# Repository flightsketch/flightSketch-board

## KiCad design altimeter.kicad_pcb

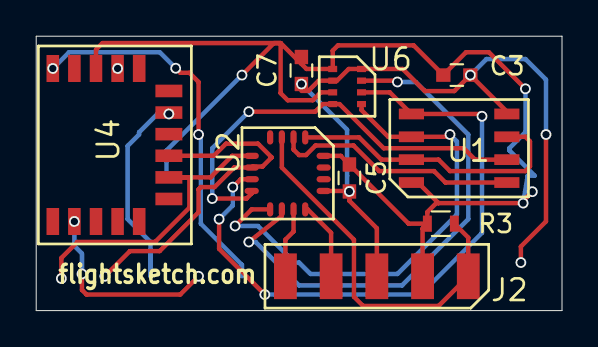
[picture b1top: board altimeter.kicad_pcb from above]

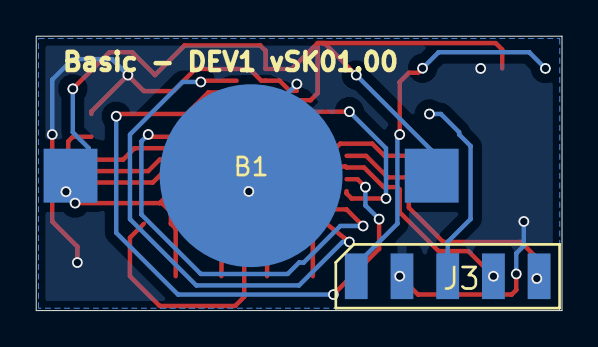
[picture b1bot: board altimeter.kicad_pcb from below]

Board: 2 copper layers, 29.2 x 15.2 mm, 11 parts (2 on the bottom side), 15 nets.

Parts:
B1: 1632-holder
C3: 10u; C_0603
C5: 0.1u; C_0603
C7: .1u; C_0603
J2, J3: Conn_01x05_Male; pin5
R3: 10k; R_0603
U1: EEPROM; SO8
U2: PIC16F15325; UQFN_16
U4: RN4871
U6: BMP280; BMP280-2

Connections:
EEPROM_CS: U1.1, U2.2
EEPROM_HOLD: U1.3, U1.7, U2.1
MCLR: J2.1, R3.1, U2.3
unnamed: J3.1, U4.16
unnamed: J3.3, U4.10
unnamed: U2.10, U6.2
PGC: J2.5, U2.11
PGD: J2.4, U2.12
SCK: U1.6, U2.9, U6.4
SDI: U1.2, U2.8, U6.5
SDO: U1.5, U2.7, U6.3
U1RX: J3.4, U2.6, U4.8
U1TX: J3.5, U2.5, U4.7
VIN: B1.2, C3.1, C5.1, C7.1, J2.2, R3.2, U1.8, U2.16, U4.14, U6.6, U6.8
VSS: B1.1, C3.2, C5.2, C7.2, J2.3, J3.2, U1.4, U2.13, U4.2, U4.13, U6.1, U6.7

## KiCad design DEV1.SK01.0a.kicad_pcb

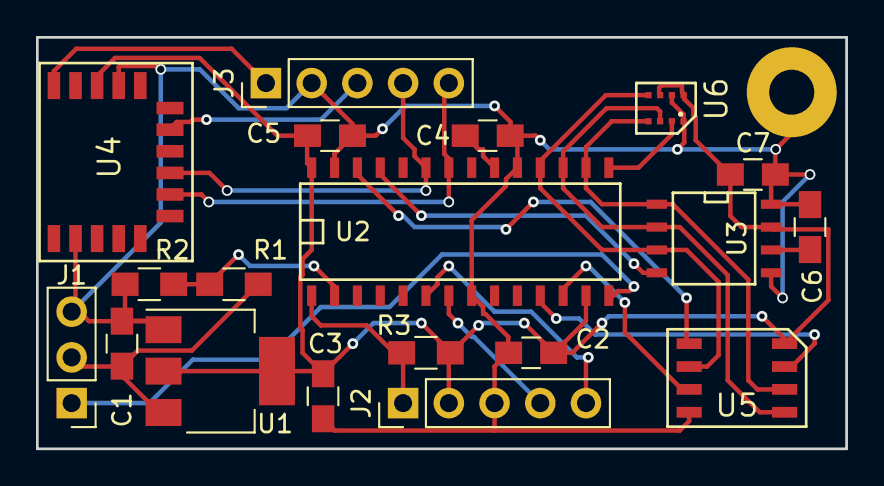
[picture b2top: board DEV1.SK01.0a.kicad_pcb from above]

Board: 2 copper layers, 45.0 x 22.9 mm, 19 parts (0 on the bottom side), 22 nets.

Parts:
C1, C3, C4: 10u; C_0805_HandSoldering
C2, C5: 0.1u; C_0805_HandSoldering
C6: 1u; C_0805_HandSoldering
C7: .1u; C_0805_HandSoldering
J1: Conn_01x03_Male; Pin_Header_Straight_1x03_Pitch2.54mm
J2, J3: Conn_01x05_Male; Pin_Header_Straight_1x05_Pitch2.54mm
R1: 200k; R_0805_HandSoldering
R2: 100k; R_0805_HandSoldering
R3: 10k; R_0805_HandSoldering
U1: LDL1117; SOT-223-3_TabPin2
U2: test; SOIC-28
U3: accel; SOIC-8-N
U4: RN4871
U5: EEPROM; SO8
U6: BMP280

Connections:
+3V3: C2.1, C3.1, C5.1, C7.1, J2.2, R3.2, U1.2, U2.13, U2.28, U3.7, U4.14, U5.8, U6.6, U6.8
DEBUG: J1.1, U2.14
MCLR: J2.1, R3.1, U2.1
unnamed: C4.1, U2.20
unnamed: C6.1, U3.6
unnamed: J3.1, U4.16
unnamed: J3.3, U4.10
unnamed: R1.1, R2.2, U2.2
unnamed: U2.11, U5.7
unnamed: U2.12, U5.3
unnamed: U2.15, U6.2
unnamed: U2.25, U3.4
unnamed: U2.26, U5.1
PGC: J2.5, U2.6
PGD: J2.4, U2.7
SCK: U2.16, U3.1, U5.6, U6.4
SDI: U2.18, U3.3, U5.2, U6.5
SDO: U2.17, U3.2, U5.5, U6.3
U1RX: J3.4, U2.23, U4.8
U1TX: J3.5, U2.22, U4.7
VIN: C1.1, J1.2, R1.2, U1.3
VSS: C1.2, C2.2, C3.2, C4.2, C5.2, C6.2, C7.2, J1.3, J2.3, J3.2, R2.1, U1.1, U2.8, U2.19, U2.27, U3.5, U3.8, U4.2, U4.13, U5.4, U6.1, U6.7

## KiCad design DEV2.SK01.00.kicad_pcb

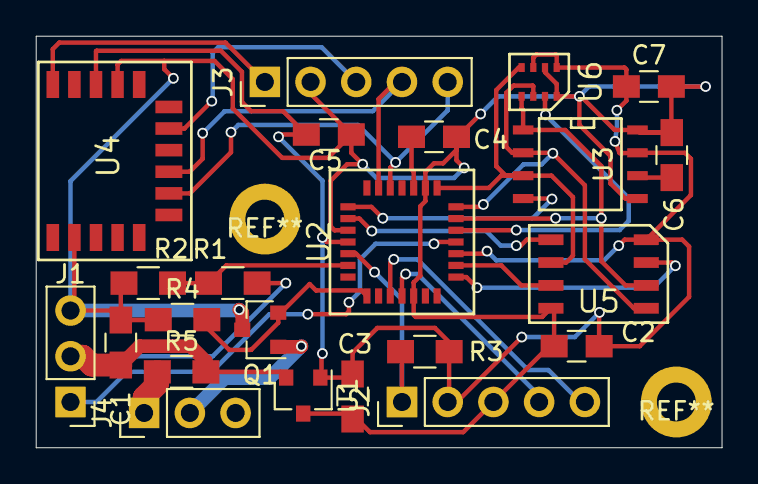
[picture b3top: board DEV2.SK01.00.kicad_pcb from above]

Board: 2 copper layers, 38.1 x 22.9 mm, 23 parts (0 on the bottom side), 25 nets.

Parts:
C1, C3, C4: 10u; C_0805_HandSoldering
C2, C5: 0.1u; C_0805_HandSoldering
C6: 1u; C_0805_HandSoldering
C7: .1u; C_0805_HandSoldering
J1, J4: Conn_01x03_Male; Pin_Header_Straight_1x03_Pitch2.54mm
J2, J3: Conn_01x05_Male; Pin_Header_Straight_1x05_Pitch2.54mm
Q1: Q_NMOS_DGS; SOT-23
R1: 200k; R_0805_HandSoldering
R2, R4, R5: 100k; R_0805_HandSoldering
R3: 10k; R_0805_HandSoldering
U1: TLV760; SOT-23
U2: test; QFN_28
U3: accel; SOIC-8-N
U4: RN4871
U5: EEPROM; SO8
U6: BMP280; BMP280-2

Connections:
+3V3: C2.1, C3.1, C5.1, C7.1, J2.2, R3.2, U1.1, U2.10, U2.25, U3.7, U4.14, U5.8, U6.6, U6.8
DEBUG: J1.1, U2.11
MCLR: J2.1, R3.1, U2.26
unnamed: C4.1, U2.17
unnamed: C6.1, U3.6
unnamed: J3.1, U4.16
unnamed: J3.3, U4.10
unnamed: J4.1, R5.1
unnamed: J4.2, Q1.1
unnamed: R1.1, R2.2, U2.27
unnamed: U2.8, U5.7
unnamed: U2.9, U5.3
unnamed: U2.12, U6.2
unnamed: U2.22, U3.4
unnamed: U2.23, U5.1
PGC: J2.5, U2.3
PGD: J2.4, U2.4
Pyro1: Q1.2, R4.2, U2.1
SCK: U2.13, U3.1, U5.6, U6.4
SDI: U2.15, U3.3, U5.2, U6.5
SDO: U2.14, U3.2, U5.5, U6.3
U1RX: J3.4, U2.20, U4.8
U1TX: J3.5, U2.19, U4.7
VIN: C1.1, J1.2, R1.2, R5.2, U1.2
VSS: C1.2, C2.2, C3.2, C4.2, C5.2, C6.2, C7.2, J1.3, J2.3, J3.2, Q1.3, R2.1, R4.1, U1.3, U2.5, U2.16, U2.24, U3.5, U3.8, U4.2, U4.13, U5.4, U6.1, U6.7

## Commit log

2018-06-04 add files
2018-06-04 remove sks
2018-06-04 strip board to basic
2018-10-05 Dev3
2018-10-05 DEV1 basic
